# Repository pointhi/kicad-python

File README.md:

# kicad-python

Abstraction layer for the KiCad python interface.

Be aware this is in initial development and the interface can change anytime!

Inspired by https://github.com/pierstitus/kicad-python

## Example usage

```python
from kicad.pcbnew import Board

b = Board.from_file('path/to/file.kicad_pcb')

for module in b.modules:
    print(module)
```

## Run Tests

```bash
./setup.py test
```

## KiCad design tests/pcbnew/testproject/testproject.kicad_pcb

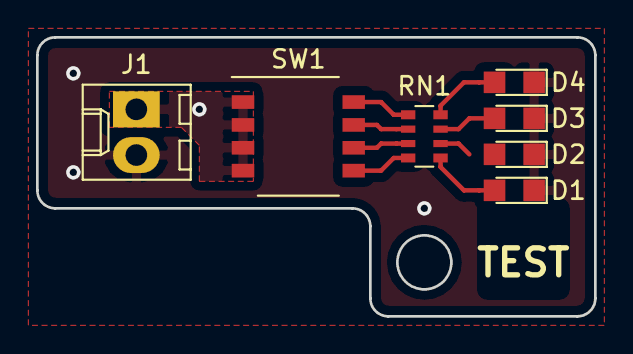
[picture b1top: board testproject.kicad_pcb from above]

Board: 2 copper layers, 31.0 x 15.5 mm, 7 parts (0 on the bottom side), 10 nets.

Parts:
D1, D2, D3, D4: LED; LED_0805
J1: Conn_01x02; Molex_KK-6410-02_02x2.54mm_Straight
RN1: R_Pack04; R_Array_Convex_4x0603
SW1: SW_DIP_x04; SW_DIP_x4_W6.15mm_Slide_Omron_A6H

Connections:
GND: D1.1, D2.1, D3.1, D4.1, J1.2
unnamed: D1.2, RN1.5
unnamed: D2.2, RN1.6
unnamed: D3.2, RN1.7
unnamed: D4.2, RN1.8
unnamed: RN1.1, SW1.8
unnamed: RN1.2, SW1.7
unnamed: RN1.3, SW1.6
unnamed: RN1.4, SW1.5
VDD: J1.1, SW1.1, SW1.2, SW1.3, SW1.4

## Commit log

2018-02-07 Currently KiCad is Python2 only
2018-02-07 Initial sphinx documentation
2018-02-07 Move into files
2018-02-07 Improve documentation
2018-02-10 Add travis and flake8 support
2018-02-10 Update README.md with Badges
2018-02-10 Fix handling of pcbnew import, so we can generate reports with sphinx
2018-02-10 Run unittests in travis
2018-02-10 Rename filename to filepath
2018-02-11 Try to write __eq__ implementations
2018-02-11 Add initial Point2D support
2018-02-17 Implement working equal operator for Module and Pad, some more implementation
2018-02-17 Fix flake8
2018-02-17 Some improvements
    * Add support for casts to the basic type
    * Add asserts to check if the object type is actually supported
    * Initial code for some new classes
2018-02-17 Add missing __ne__ overrides, add some comment to get_native
2018-02-17 Add some drawsegment implementation
2018-02-17 Some little renaming
2018-02-17 Move kicad.pcbnew.Line to other location in file
2018-02-17 Fix super declaration
2018-03-03 Add BoardItem parent class, some new methods
2018-03-03 Some little style fixes
2018-03-03 Fix formating
2018-03-03 Add testcase for from_file, add example project for further tests
2018-03-03 Add more Drawsegment implementation details, Layer support
2018-03-03 Use __eq__ implementation from BoardItem instead of specialisation
2018-03-03 Add kicad.pcbnew.dimension implementation
2018-03-03 Add initial implementation of kicad.pcbnew.PcbTarget
2018-03-06 Add initial Net support
2018-03-06 Fix setup.py
2018-03-06 Fix sphinx integration
2018-03-06 Fix PEP8
2018-03-06 Now sphinx should be fixed again
2018-03-06 Add BoardItemLayer object and add normal Layer object
2018-03-06 Add initial plotter support
2018-03-06 Fix plotter
2018-03-06 Fix doctest
2018-03-06 Fix type in docstring
2018-08-02 Make first pre-alpha release (v.0.0.1)
2018-08-02 Fix text representation in PyPI for next point release
2018-08-04 Add more implementation and first example
2018-08-04 Add Python 3 compability
2018-08-06 Add real example to docs
2018-08-06 Fix some Python 3 compatiblity issues
2018-08-28 Implement missing API parts
2018-08-28 Extend sphinx documentation with new classes
2018-08-28 Add missing __hash__ methods to support dictionaries
2018-08-28 Add initial code for difftool
2018-08-28 Finish initial diff viewer
2018-08-28 Some small improvements to the diff-tool
2018-08-28 Little fixes, release v0.0.2
2018-09-09 Add initial mypy support
    Add a static type checker to catch some more bugs
2018-09-09 Add some initial typehints
2018-09-09 Fix some typehinting issue
2018-09-14 Add support for read/write of KiCad Boards and Footprints
2018-09-14 Initial version of footprint wizard implementation
    Only some hacky proposal which works on CMD as well as in KiCad GUI.
    Many things are preliminary to get it working. Ideas are welcome.
2018-09-14 Fix flake8 error
2018-09-26 Add example where we specify minimal drill and annular size
2018-09-26 Fix x/y confusion in example file
2018-09-26 Fix typo in example
2018-09-26 Fix: skipping of SMD pads in example
2018-09-26 fixed indention, mumble mumble...
2019-02-10 try new nightly builds
2019-03-15 Fix security issue when loading yaml
    https://github.com/yaml/pyyaml/wiki/PyYAML-yaml.load(input)-Deprecation
2021-10-20 fix kicad.org link
